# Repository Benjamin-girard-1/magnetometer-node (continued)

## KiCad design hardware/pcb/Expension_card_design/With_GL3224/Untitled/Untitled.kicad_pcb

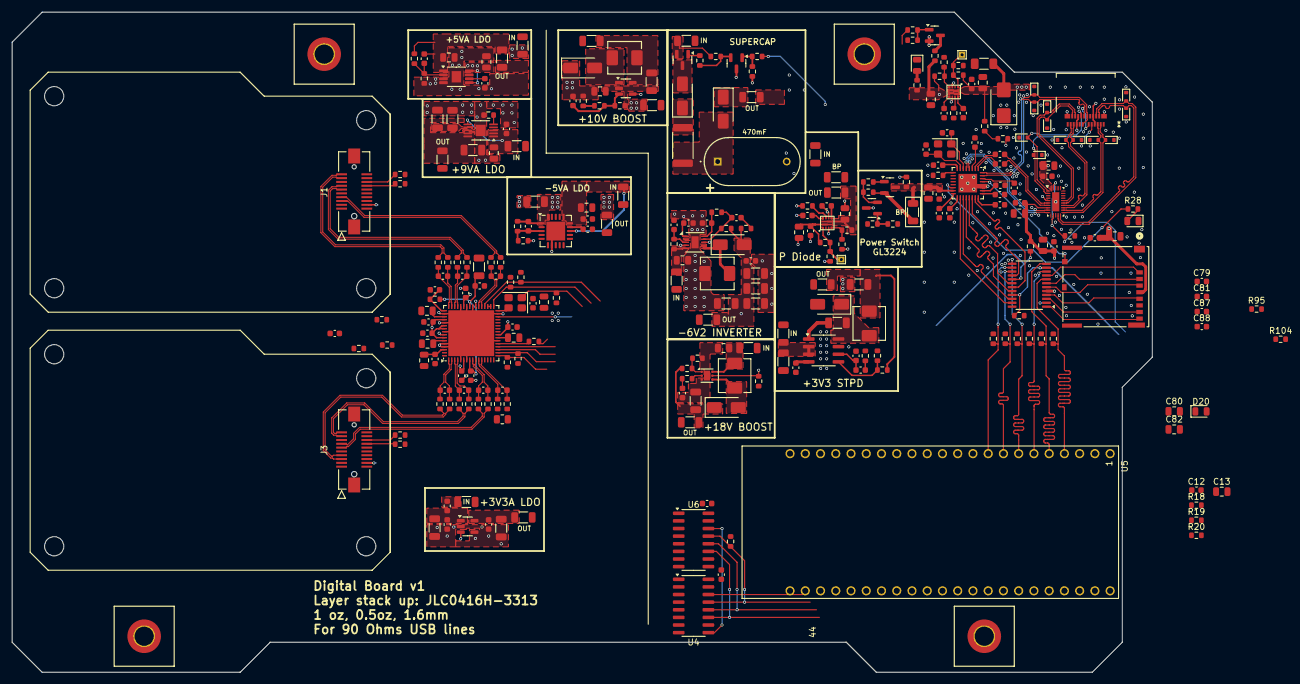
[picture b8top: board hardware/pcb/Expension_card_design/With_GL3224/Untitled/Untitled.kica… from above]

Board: 4 copper layers, 190.0 x 110.0 mm, 282 parts (0 on the bottom side), 194 nets.

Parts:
C1, C7, C13, C17, C23, C34#2, C36, C51, C60, C62, C66, C72, C82: 10u; C_0805_2012Metric
C2, C6, C9, C10, C32#2, C35, C74, C75, C76, C77: 4u7; C_1206_3216Metric
C3, C18, C28, C29, C61, C63, C68, C73: 10n; C_0603_1608Metric
C4: 22p; C_0603_1608Metric
C5, C15, C20, C32, C57, C58, C59, C80, C83, C86, C91: 1u; C_0805_2012Metric
C8, C11, C12, C14, C16, C21, C31, C33, C33#2, C34, C37, C38, C39, C40, C41, C42, C43, C50, C53, C54, C56, C64, C67, C71, C79, C81, C84, C85, C87, C88, C92, C93, C94, C95, C96, C97, C98, C98#2, C99, C99#2, C100: 100n; C_0603_1608Metric
C19, C30, C44, C45, C47, C48, C49, C52: 1n; C_0603_1608Metric
C22, C24: 22u; C_1206_3216Metric
C25, C55, C69: 47u; C_1206_3216Metric
C26, C78: 4n7; C_0603_1608Metric
C27, C70: 10p; C_0603_1608Metric
C31#2: 470mF; C_Radial_D8.0mm_P11.50mm
C46, C65: 220n; C_0603_1608Metric
C89, C90: 18p; C_0603_1608Metric
D1, D2, D16, D17, D18, D19: SS34; D_SMA
D3: KT-0805G; LED_0805_2012Metric
D3#2: P6SMB6.8CA; D_SMB
D4, D5, D6, D7, D8, D9, D10, D11, D12, D13, D14, D15: H5VUD5BB; D_SOD-523
D5#2, D20: NCD0805R1; LED_0805_2012Metric
FB1: FerriteBead; L_0603_1608Metric
H1, H2, H3, H4: PCB_MountingHole; MountingHole_3.2mm_M3_DIN965_Pad_TopBottom
J1, J3: 550910274; Expansion_card
J2: USB_C_RECEPTACLE_MOLEX; CONN_201267-0005_MOL
J4: Micro_SD_CARD; CONN_503398-1892_MOL
L1, L2, L3, L4: 10u; L_Sunlord_MWSA0503S
Q1, Q3, Q5: AO3400A; SOT-23
Q2, Q4: AO3401A; SOT-23
R1, R2, R9, R10, R11, R15, R31, R32, R33, R34, R37, R44, R49, R51, R52#2, R80, R81, R84, R85, R90, R93, R112: 0; R_1206_3216Metric
R3: 49k9; R_0603_1608Metric
R4, R7, R8, R17, R23, R30, R36, R50, R52, R53, R54, R57, R71, R74, R76, R78, R86, R89, R92, R94, R95, R105, R111: 100k; R_0603_1608Metric
R5, R21, R25, R41, R59, R96, R97, R98, R99, R100, R101: 10k; R_0603_1608Metric
R6: 3k6; R_0603_1608Metric
R12, R91: 510k; R_0603_1608Metric
R13, R28, R56, R63, R66, R79, R104: 1k; R_0603_1608Metric
R14, R24, R38: 200k; R_0603_1608Metric
R16: 90k9; R_1206_3216Metric
R18, R19, R20, R58, R60, R61, R62, R64, R65, R67, R69, R70, R72, R73, R75, R77: 22; R_0603_1608Metric
R22, R35, R102, R103: 470k; R_0603_1608Metric
R25#2, R39, R45, R82, R107: 39k; R_0603_1608Metric
R26: R_1206_3216Metric_Pad1.30x1.75mm_HandSolder
R27, R43: 2k; R_0603_1608Metric
R28#2, R29, R46, R47, R108, R109: 100; R_0603_1608Metric
R40: 75k; R_0603_1608Metric
R42: 24k; R_0603_1608Metric
R48: 22; R_2512_6332Metric
R55: 300k; R_0603_1608Metric
R68: 2k4; R_0805_2012Metric
R83: 12k; R_0603_1608Metric
R87, R110: 330k; R_0603_1608Metric
R88: 10; R_0603_1608Metric
R106: 680; R_0603_1608Metric
TP1, TP2: TestPoint; TestPoint_THTPad_1.0x1.0mm_Drill0.5mm
U1: TPS61170; WSON-6-1EP_2x2mm_P0.65mm_EP1x1.6mm
U2: LT3042xMSE; MSOP-10-1EP_3x3mm_P0.5mm_EP1.68x1.88mm
U3: TPS61040DBV; SOT-23-5
U4, U6: 74HC595D,118; SOIC-16_3.9x9.9mm_P1.27mm
U5: ESP32-S3-DevKitC; MODULE_ESP32-S3-DEVKITC
U7, U8: TPS25210LRPWR; VQFN-HR-10
U9: TPS54331DR; SOIC-8_3.9x4.9mm_P1.27mm
U10: TPS7A2033PDBVR; SOT-23-5
U11: AD7779; QFN-64-1EP_9x9mm_P0.5mm_EP7.65x7.65mm
U12: TPS7A4901DGNR; HVSSOP-8-1EP_3x3mm_P0.65mm_EP1.57x1.89mm
U13: TPS7A3301RGWR; Texas_RGW0020A_VQFN-20-1EP_5x5mm_P0.65mm_EP3.15x3.15mm
U14: TPS63700DRCR; VSON-10-1EP_3x3mm_P0.5mm_EP1.2x2mm
U15: TS3A27518ERTW; TSSOP-24_4.4x7.8mm_P0.65mm
U16: GL3224-OIY04; QFN-32-1EP_5x5mm_P0.5mm_EP3.1x3.1mm
U17: HD3SS3220RNHR; Texas_RNH0030A_WQFN-30-1EP_2.5x4.5mm_P0.4mm_EP1.2x3.2mm
Y1: OT2JI-111-8.192M; Crystal_SMD_3225-4Pin_3.2x2.5mm
Y2: X322525MOB4SI; Crystal_SMD_3225-4Pin_3.2x2.5mm

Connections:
+1V65: J1.12, J3.12, U11.57 (VCM)
+3V3: C11.1, C12.1, C13.1, C14.1, C31.1, C32.2, C33.1, C34#2.1, C42.1, C50.1, C51.1, C79.1, C80.2, C81.1, C82.1, C83.2, C84.1, J4.4 (VDD), R21.1, R37.2, R52.1, R59.2, R76.1, R78.1, R94.1, R95.1, R96.1, R97.1, R98.1, R99.1, R100.1, R101.1, U4.16 (VCC), U5.1 (ESP_3V3), U5.2 (ESP_3V3), U6.16 (VCC), U7.3 (PG), U8.3 (PG), U11.24 (IOVDD), U15.5 (VCC), U17.8 (VCC33), Y1.4 (VDD)
+3V3A: C36.1, C37.1, C38.1, C39.1, C40.1, C41.1, J1.2, J3.2, R52#2.2, R63.1, U11.6 (AVDD1A), U11.43 (AVDD1B), U11.52 (AVDD2B), U11.54 (FORMAT1), U11.55 (FORMAT0), U11.58 (AVDD2A), U11.62 (AVDD4)
+5V: C17.1, C85.1, C86.2, Q4.2 (S), R1.1, R15.1, R23.1, R25.1, R28#2.1, R31.1, R32.1, R44.1, R51.1, R90.1, R107.1, R112.2, U7.6 (OUT), U17.30 (VDD5)
+5VA: J1.14, J3.14, R80.2
+9VA: J1.16, J3.16, R11.2, R55.1
+18V: J1.13, J3.13, R2.2
-5VA: J1.15, J3.15, R85.2
/ADC_AD777x/ADC_9VA_MON: C43.1, R55.2, R56.1, R57.1
/ADC_AD777x/ADC_9VA_MON_FLT: R56.2, U11.39 (AIN6+)
/ADC_AD777x/ADC_AREG1CAP: C58.1, U11.59 (AREG1CAP)
/ADC_AD777x/ADC_AREG2CAP: C59.1, U11.51 (AREG2CAP)
/ADC_AD777x/ADC_CONVST_SAR: R71.1, U6.4 (QE), U11.17 (CONVST_SAR)
/ADC_AD777x/ADC_CS: R18.1, R59.1, U11.18 (ALERT/~CS)
/ADC_AD777x/ADC_DREGCAP: C57.1, U11.23 (DREGCAP)
/ADC_AD777x/ADC_IN0+: C44.1, R58.2, U11.2 (AIN0+)
/ADC_AD777x/ADC_IN0-: C44.2, R60.2, U11.1 (AIN0-)
/ADC_AD777x/ADC_IN1+: C45.1, R61.2, U11.4 (AIN1+)
/ADC_AD777x/ADC_IN1-: C45.2, R64.2, U11.3 (AIN1-)
/ADC_AD777x/ADC_IN2+: C47.1, R65.2, U11.10 (AIN2+)
/ADC_AD777x/ADC_IN2-: C47.2, R67.2, U11.9 (AIN2-)
/ADC_AD777x/ADC_IN3+: C52.1, R75.2, U11.37 (AIN7+)
/ADC_AD777x/ADC_IN3-: C52.2, R77.2, U11.38 (AIN7-)
/ADC_AD777x/ADC_IN4+: C48.1, R69.2, U11.47 (AIN4+)
/ADC_AD777x/ADC_IN4-: C48.2, R70.2, U11.48 (AIN4-)
/ADC_AD777x/ADC_IN5+: C49.1, R72.2, U11.45 (AIN5+)
/ADC_AD777x/ADC_IN5-: C49.2, R73.2, U11.46 (AIN5-)
/ADC_AD777x/ADC_MCLK: U11.32 (XTAL2/MCLK), Y1.3 (OUT)
/ADC_AD777x/ADC_MCLK_EN: R78.2, U6.7 (QH), Y1.1 (Tri-State)
/ADC_AD777x/ADC_REF+: C53.1, C54.1, C55.1, R79.1, U11.8 (REF1+), U11.41 (REF2+)
/ADC_AD777x/ADC_REF_OUT: C56.1, R79.2, U11.49 (REF_OUT)
/ADC_AD777x/ADC_RESET: R76.2, U6.6 (QG), U11.36 (~RESET)
/ADC_AD777x/ADC_SCLK: R19.1, U11.19 (DCLK2/SCLK)
/ADC_AD777x/ADC_SDI: R20.1, U11.20 (DCLK1/SDI)
/ADC_AD777x/ADC_SDO_R: R62.1, U11.21 (DCLK0/SDO)
/ADC_AD777x/ADC_START: R74.1, U6.5 (QF), U11.33 (~START)
/ADC_AD777x/AIN0+: J3.3, R60.1
/ADC_AD777x/AIN0-: J3.4, R58.1
/ADC_AD777x/AIN1+: J3.7, R67.1
/ADC_AD777x/AIN1-: J3.6, R65.1
/ADC_AD777x/AIN2+: J3.10, R61.1
/ADC_AD777x/AIN2-: J3.9, R64.1
/ADC_AD777x/AIN3+: J1.4, R75.1
/ADC_AD777x/AIN3-: J1.3, R77.1
/ADC_AD777x/AIN4+: J1.7, R73.1
/ADC_AD777x/AIN4-: J1.6, R72.1
/ADC_AD777x/AIN5+: J1.9, R69.1
/ADC_AD777x/AIN5-: J1.10, R70.1
/ADC_AD777x/PT1000_AIN+: C46.1, R63.2, U11.12 (AIN3+)
/ADC_AD777x/PT1000_AIN-: C46.2, R66.2, U11.11 (AIN3-)
/ADC_AD777x/PT1000_DRAIN: R66.1, R68.2
/DATA_SAVING/+5VBUS_DATA: C15.1, C16.1, D3#2.2 (A2), J2.A4 (VBUS), J2.A9 (VBUS), J2.B4 (VBUS), J2.B9 (VBUS), R22.1, R26.2, R102.1, U7.5 (IN)
/DATA_SAVING/AVDD12: C99#2.1, U16.3 (AVDD12)
/DATA_SAVING/AVDD33: C98#2.1, U16.30 (AVDD33)
/DATA_SAVING/AVDD33_: C97.1, U16.8 (AVDD33)
/DATA_SAVING/CC1: D5.2, J2.A5 (CC1), U17.2 (CC1)
/DATA_SAVING/CC2: D4.2, J2.B5 (CC2), U17.1 (CC2)
/DATA_SAVING/DATA_D+: D15.2, J2.A6 (D+), J2.B6 (D+), U16.32 (DP)
/DATA_SAVING/DATA_D-: D14.2, J2.A7 (D-), J2.B7 (D-), U16.31 (DM)
/DATA_SAVING/DVDD12: C100.1, U16.17 (DVDD12)
/DATA_SAVING/DVDD33: C94.1, U16.25 (DVDD33)
/DATA_SAVING/DVDD33_: C93.1, U16.16 (DVDD33)
/DATA_SAVING/EN_SD_MUX: R52.2, R95.2, U4.6 (QG), U15.17 (~EN)
/DATA_SAVING/EN_USB_MUX: R105.1, U4.5 (QF), U17.12 (ENn_MUX), U17.29 (ENn_CC)
/DATA_SAVING/EN_USB_READ: R109.2, U4.7 (QH)
/DATA_SAVING/EN_USB_READ_G: Q5.1 (G), R109.1, R111.1
/DATA_SAVING/E_CLK: R98.2, U5.5 (GPIO5), U15.12 (NO3)
/DATA_SAVING/E_CMD: R99.2, U5.9 (GPIO16), U15.14 (NO4)
/DATA_SAVING/E_D0: R97.2, U5.6 (GPIO5), U15.10 (NO2)
/DATA_SAVING/E_D1: R96.2, U5.4 (GPIO4), U15.8 (NO1)
/DATA_SAVING/E_D2: R101.2, U5.7 (GPIO7), U15.13 (NO6)
/DATA_SAVING/E_D3: R100.2, U5.8 (GPIO15), U15.15 (NO5)
/DATA_SAVING/GL3224_X1: C89.1, U16.6 (X1), Y2.1
/DATA_SAVING/GL3224_X2: C90.1, U16.7 (X2), Y2.3
/DATA_SAVING/GL_CLK: U15.20 (NC3), U16.20 (SD_CK)
/DATA_SAVING/GL_CMD: U15.18 (NC4), U16.21 (SD_CM)
/DATA_SAVING/GL_D0: U15.22 (NC2), U16.19 (SD_D0)
/DATA_SAVING/GL_D1: U15.23 (NC1), U16.18 (SD_D1)
/DATA_SAVING/GL_D2: U15.19 (NC6), U16.23 (SD_D2)
/DATA_SAVING/GL_D3: U15.16 (NC5), U16.22 (SD_D3)
/DATA_SAVING/LED: R104.1, U16.14 (LED)
/DATA_SAVING/MCLK: J4.5 (CLK), U15.4 (COM3)
/DATA_SAVING/MCMD: J4.3 (CMD), U15.6 (COM4)
/DATA_SAVING/MD0: J4.7 (DAT0), U15.3 (COM2)
/DATA_SAVING/MD1: J4.8 (DAT1), U15.1 (COM1)
/DATA_SAVING/MD2: J4.1 (DAT2), U15.9 (COM6)
/DATA_SAVING/MD3: J4.2 (DAT3), U15.7 (COM5)
/DATA_SAVING/RTERM: R106.2, U16.9 (RTERM)
/DATA_SAVING/RX1+: D9.2, J2.B11 (RX1+), U17.15 (RX1p)
/DATA_SAVING/RX1-: D8.2, J2.B10 (RX1-), U17.14 (RX1n)
/DATA_SAVING/RX2+: D7.2, J2.A10 (RX2-), U17.18 (RX2p)
/DATA_SAVING/RX2-: D6.2, J2.A11 (RX2+), U17.19 (RX2n)
/DATA_SAVING/SD_MUX_SEL: R94.2, U4.15 (QA), U15.11 (IN2), U15.21 (IN1)
/DATA_SAVING/SD_VCC: C96.1, U16.26 (SD_VCC)
/DATA_SAVING/TX1+: D12.2, J2.A3 (TX1-), U17.17 (TX1p)
/DATA_SAVING/TX1-: D13.2, J2.A2 (TX1+), U17.16 (TX1n)
/DATA_SAVING/TX2+: D10.2, J2.B3 (TX2-), U17.21 (TX2p)
/DATA_SAVING/TX2-: D11.2, J2.B2 (TX2+), U17.20 (TX2n)
/DATA_SAVING/USB_GL_TX+: C87.2, C98.2, U16.2 (TXP)
/DATA_SAVING/USB_GL_TX-: C88.2, C99.2, U16.1 (TXN)
/DATA_SAVING/USB_HD_TX+: C87.1, C98.1, U17.6 (TXp)
/DATA_SAVING/USB_HD_TX-: C88.1, C99.1, U17.7 (TXn)
/DATA_SAVING/USB_RX+: U16.5 (RXP), U17.9 (RXp)
/DATA_SAVING/USB_RX-: U16.4 (RXN), U17.10 (RXn)
/DATA_SAVING/USB_SW_GATE: Q4.1 (G), R108.2
/DATA_SAVING/USB_SW_GDRV: Q5.2 (S), R107.2, R108.1
/DATA_SAVING/VBUS_USB_SW: C91.2, C92.1, Q4.3 (D), R110.2, R112.1, U16.15 (VBUS)
/DATA_SAVING/VUHSI: C95.1, U16.24 (VUHSI)
/IO_CONNECTOR/5VDAT_EFUSE_DVDT: C19.1, U7.7 (dV/dt)
/IO_CONNECTOR/5VDAT_EFUSE_EN_ULVO: R22.2, R24.1, TP1.1, U7.1 (EN/ULVO)
/IO_CONNECTOR/5VDAT_EFUSE_ILM: R27.1, U7.9 (ILM)
/IO_CONNECTOR/5VDAT_EFUSE_ITIMER: C18.1, U7.10 (ITIMER)
/IO_CONNECTOR/5VDAT_EFUSE_PGTH: R23.2, R25#2.1, U7.4 (PGTH)
/IO_CONNECTOR/EN_KEEPALIVE_GATE: Q1.1 (G), R29.2, R30.1
/IO_CONNECTOR/KEEPALIVE_DRAIN: Q1.3 (D), R28#2.2
/MCU_ESP32S3/EN_BST_10V: U3.4 (EN), U4.2 (QC)
/MCU_ESP32S3/EN_BST_18V: R4.1, U1.5 (CTRL), U4.3 (QD)
/MCU_ESP32S3/EN_INV_-5V: U4.4 (QE), U14.4 (EN)
/MCU_ESP32S3/EN_LDO_3V3: U4.1 (QB), U10.3 (EN)
/MCU_ESP32S3/SR_CHAIN_DATA: U4.9 (QH'), U6.14 (SER)
/MCU_ESP32S3/SR_LATCH: U4.12 (RCLK), U6.12 (RCLK)
/MCU_ESP32S3/SR_OE_N: R21.2, U4.13 (~OE), U6.13 (~OE)
/MCU_ESP32S3/SR_SHIFT_CLK: U4.11 (SRCLK), U6.11 (SRCLK)
/PWR_3V3A/+5V_IN: FB1.1, R51.2
/PWR_3V3A/LDO_3V3_IN: C32#2.1, C33#2.1, FB1.2, U10.1 (IN)
/PWR_3V3A/LDO_3V3_OUT: C34.1, C35.1, R52#2.1, U10.5 (OUT)
/PWR_3V3D/3V3D_EFUSE_DVDT: C30.1, U8.7 (dV/dt)
/PWR_3V3D/3V3D_EFUSE_EN_ULVO: R35.2, R38.1, TP2.1, U8.1 (EN/ULVO)
/PWR_3V3D/3V3D_EFUSE_ILM: R43.1, U8.9 (ILM)
/PWR_3V3D/3V3D_EFUSE_ITIMER: C29.1, U8.10 (ITIMER)
/PWR_3V3D/3V3D_EFUSE_PGTH: R36.2, R39.1, U8.4 (PGTH)
/PWR_3V3D/5V_HOLDUP_CAP: R31.2, R33.2, R34.1, R49.2
/PWR_3V3D/5V_HOLDUP_DIODE: C23.1, R33.1, R36.1, U8.6 (OUT)
/PWR_3V3D/5V_HOLDUP_IN: C24.1, R34.2, U9.2 (VIN), U9.3 (EN)
/PWR_3V3D/5V_SUPERCAP: C31#2.1, D18.2 (A), R48.2
/PWR_3V3D/+3V3_OUT: C25.1, L3.2, R37.1, R40.1
/PWR_3V3D/+5V_IN: C20.1, C21.1, R32.2, R35.1, U8.5 (IN)
/PWR_3V3D/+5V_SUPERCAP_IN: Q2.2 (S), R44.2, R45.1
/PWR_3V3D/STPD_3V3_BOOT: C22.1, U9.1 (BOOT)
/PWR_3V3D/STPD_3V3_COMP: C26.1, C27.1, U9.6 (COMP)
/PWR_3V3D/STPD_3V3_COMP_F: C26.2, R41.1
/PWR_3V3D/STPD_3V3_PH: C22.2, D16.1 (K), L3.1, U9.8 (PH)
/PWR_3V3D/STPD_3V3_SS: C28.1, U9.4 (SS)
/PWR_3V3D/STPD_3V3_VSENS: R40.2, R42.1, U9.5 (VSENSE)
/PWR_5VA_NEG5/+5VA_OUT: C61.1, C62.1, R80.1, R82.1, U12.1 (OUT)
/PWR_5VA_NEG5/+5V_IN_N5V: C72.1, R88.2, R90.2, U14.5 (IN)
/PWR_5VA_NEG5/+10V_IN_LDO: C60.1, R81.2, U12.5 (EN), U12.8 (IN)
/PWR_5VA_NEG5/INV_N5V5_COMP: C78.1, U14.1 (COMP)
/PWR_5VA_NEG5/INV_N5V5_FB: C70.1, R86.2, R91.1, U14.9 (FB)
/PWR_5VA_NEG5/INV_N5V5_FF: C70.2, R92.1
/PWR_5VA_NEG5/INV_N5V5_SW: D19.1 (K), L4.1, U14.6 (SW)
/PWR_5VA_NEG5/INV_N5V5_VIN: C64.1, R88.1, U14.3 (VIN)
/PWR_5VA_NEG5/INV_N5V5_VREF: C65.1, R86.1, U14.10 (VREF)
/PWR_5VA_NEG5/LDO_N5V_FB: C68.2, R87.2, R89.1, U13.3 (FB)
/PWR_5VA_NEG5/LDO_N5V_NR: C71.1, U13.14 (NR/SS)
/PWR_5VA_NEG5/LDO_P5V_FB: C61.2, R82.2, R83.1, U12.2 (FB)
/PWR_5VA_NEG5/LDO_P5V_NR: C63.1, U12.6 (NR/SS)
/PWR_5VA_NEG5/N5V: R84.1, R93.2
/PWR_5VA_NEG5/N5V5_PRE_N5VA: C73.1, C74.1, C75.1, C76.1, C77.1, D19.2 (A), R91.2, R92.2, R93.1, U14.8 (OUT)
/PWR_5VA_NEG5/N5V_VIN_LDO: C66.1, C67.1, R84.2, U13.13 (EN), U13.15 (IN), U13.16 (IN)
/PWR_5VA_NEG5/N5V_VOUT_LDO: C68.1, C69.1, R85.1, R87.1, U13.1 (OUT), U13.20 (OUT)
/PWR_9V_BRIDGE/+5V_IN_BST: C10.1, L2.1, R15.2, U3.5 (VIN)
/PWR_9V_BRIDGE/+9V_LDO_OUT: C6.1, R11.1, U2.9 (OUTS), U2.10 (OUT)
/PWR_9V_BRIDGE/+10V: R9.2, R10.1, R81.1
/PWR_9V_BRIDGE/+10V_LDO_IN: C7.1, C8.1, R10.2, U2.1 (IN), U2.2 (IN), U2.3 (EN/UV), U2.6 (PGFB)
/PWR_9V_BRIDGE/+10V_OUT: C4.1, C5.1, D2.1 (K), R9.1, R12.1
/PWR_9V_BRIDGE/BST_10V_FB: C4.2, R14.2, R17.1, U3.3 (FB)
/PWR_9V_BRIDGE/BST_10V_FB_DIV: R12.2, R14.1
/PWR_9V_BRIDGE/BST_10V_SW: D2.2 (A), L2.2, U3.1 (SW)
/PWR_9V_BRIDGE/LDO_9V_ILIM: R13.2, U2.5 (ILIM)
/PWR_9V_BRIDGE/LDO_9V_SET: C9.1, R16.1, U2.7 (SET)
/RESET_1: J3.18, R53.1, U6.2 (QC)
/RESET_2: J1.18, R7.1, U6.15 (QA)
/SENSOR_SET_RESET_DRIVER/+18V_OUT: C2.1, D1.1 (K), R2.1, R3.1
/SENSOR_SET_RESET_DRIVER/BST_18V_COMP: R5.1, U1.2 (COMP)
/SENSOR_SET_RESET_DRIVER/BST_18V_COMP_FILT: C3.1, R5.2
/SENSOR_SET_RESET_DRIVER/BST_18V_FB: R3.2, R6.1, U1.1 (FB)
/SENSOR_SET_RESET_DRIVER/BST_18V_IN: C1.1, L1.1, R1.2, U1.6 (VIN)
/SENSOR_SET_RESET_DRIVER/BST_18V_SW: D1.2 (A), L1.2, U1.4 (SW)
/SET_1: J3.17, R54.1, U6.3 (QD)
/SET_2: J1.17, R8.1, U6.1 (QB)
GND: C1.2, C2.2, C3.2, C5.2, C6.2, C7.2, C8.2, C9.2, C10.2, C11.2, C12.2, C13.2, C14.2, C15.2, C16.2, C17.2, C18.2, C19.2, C20.2, C21.2, C23.2, C24.2, C25.2, C27.2, C28.2, C29.2, C30.2, C31.2, C31#2.2, C32.1, C32#2.2, C33.2, C33#2.2, C34.2, C34#2.2, C35.2, C36.2, C37.2, C38.2, C39.2, C40.2, C41.2, C42.2, C43.2, C50.2, C51.2, C53.2, C54.2, C55.2, C56.2, C57.2, C58.2, C59.2, C60.2, C62.2, C63.2, C64.2, C65.2, C66.2, C67.2, C69.2, C71.2, C72.2, C73.2, C74.2, C75.2, C76.2, C77.2, C78.2, C79.2, C80.1, C81.2, C82.2, C83.1, C84.2, C85.2, C86.1, C89.2, C90.2, C91.1, C92.2, C93.2, C94.2, C95.2, C96.2, C97.2, C98#2.2, C99#2.2, C100.2, D3.1 (K), D3#2.1 (A1), D4.1, D5.1, D5#2.1 (K), D6.1, D7.1, D8.1, D9.1, D10.1, D11.1, D12.1, D13.1, D14.1, D15.1, D16.2 (A), D20.1 (K), H1.1, H2.1, H3.1, H4.1, J1.5, J1.8, J1.11, J1.P1, J1.P2, J2.A1 (GND), J2.A12 (GND), J2.B1 (GND), J2.B12 (GND), J3.5, J3.8, J3.11, J3.P1, J3.P2, J4.6 (VSS), J4.10 (SHIELD), J4.11 (VSS), J4.12 (VSS), J4.13 (VSS), J4.14 (VSS), L4.2, Q1.2 (S), Q3.3 (D), Q5.3 (D), R4.2, R6.2, R7.2, R8.2, R13.1, R16.2, R17.2, R24.2, R25#2.2, R26.1, R27.2, R30.2, R38.2, R39.2, R41.2, R42.2, R43.2, R50.2, R53.2, R54.2, R57.2, R68.1, R71.2, R74.2, R83.2, R89.2, R105.2, R106.1, R110.1, R111.2, U1.3 (GND), U1.7 (TP), U2.8 (GND), U2.11 (GND), U3.2 (GND), U4.8 (GND), U5.22 (GND), U5.23 (GND), U5.43 (GND), U5.44 (GND), U6.8 (GND), U7.8 (GND), U8.8 (GND), U9.7 (GND), U10.2 (GND), U10.4 (NC), U11.5 (AVSS1A), U11.7 (REF1-), U11.22 (DGND), U11.31 (XTAL1), U11.40 (AIN6-), U11.42 (REF2-), U11.44 (AVSS1B), U11.50 (AVSS2B), U11.53 (AVSS3), U11.56 (CLK_SEL), U11.60 (AVSS2A), U11.61 (AVSS4), U11.65 (EPAD(AVSSx)), U12.3 (NC), U12.4 (GND), U12.9 (PwPd), U13.7 (GND), U13.21 (EP), U14.2 (GND), U14.7 (PSGND), U14.11 (PowerPAD), U15.2 (GND), U16.27 (GND), U16.28 (SD_WP), U16.33 (GND), U17.4 (PORT), U17.13 (GND), U17.28 (GND), U17.31 (GND), Y1.2 (GND), Y2.2, Y2.4
unnamed: D3.2 (A), R25.2
unnamed: D5#2.2 (A), R28.2
unnamed: D17.2 (A), Q2.3 (D)
unnamed: D17.1 (K), R48.1
unnamed: D18.1 (K), R49.1
unnamed: D20.2 (A), R104.2
unnamed: Q2.1 (G), R46.2
unnamed: Q3.1 (G), R47.1, R50.1
unnamed: Q3.2 (S), R45.2, R46.1
unnamed: R102.2, R103.1
unnamed: U11.34 (~SYNC_OUT), U11.35 (~SYNC_IN)
unnamed: R103.2, U17.5 (VBUS_DET)

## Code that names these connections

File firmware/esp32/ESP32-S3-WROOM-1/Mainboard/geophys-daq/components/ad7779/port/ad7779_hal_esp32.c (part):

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 * @brief AD7779 HAL implementation for ESP32-S3 / ESP-IDF.
 *
 * Pinout (per project schematic):
 *   ADC_DRDY -> GPIO10  (input, falling edge IRQ)
 *   ADC_CS   -> GPIO11  (output, active low — manually controlled)
 *   ADC_SCLK -> GPIO12
 *   ADC_SDI  <- GPIO13  (ESP MOSI -> AD7779 SDI)
 *   ADC_SDO  -> GPIO14  (ESP MISO <- AD7779 SDO)
 *
 * Architecture:
 *   - Manual CS via GPIO (the SPI peripheral's hardware CS routing
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
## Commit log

2025-11-18 initial Kicad commit
2025-11-19 Schematic sensor stage done
2025-12-11 pre SPI test
2026-01-07 esp32_testing
2026-04-30 first code for the v1
2026-04-30 SCL3300 driver functionnal
2026-05-01 Somewhat fix the ad7779 driver to read the thermistor but error with divider
2026-05-05 Bring up thermistor logging with IMU temperature references
2026-05-25 Backup avant deletion offset/dac
2026-05-27 SD mux and 3V3D power sequencing bring-up
2026-05-28 ADC_Fixed
2026-06-01 Python app works as I want
2026-06-02 ADC Works! Gain is normal
2026-06-03 calibration on the z and x axis
2026-06-09 Work in progress rev2
2026-06-15 Ignore CSV data files
2026-06-22 Delete hardware/pcb/lib.zip
    delete
2026-06-22 Delete hardware/pcb/Expension_card_design/PCB.zip
    pcb.zip delete
2026-06-23 clearing git
2026-06-26 kicad mag board done
